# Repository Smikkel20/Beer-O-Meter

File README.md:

# Beer-O-Meter

A fun ATTiny-powered device that measures how quickly you can down a pint. Place a glass on the pressure plate, press the button, drink, and release — the 7-segment display shows your elapsed time in centiseconds.

## Features

- **Pressure plate / button trigger** — starts timing when pressed, stops when released.
- **TM1637 4-digit 7-segment display** — shows elapsed time live.
- **Auto-reset** — after a short cooldown, the meter is ready for the next round.
- **KiCad PCB** — custom PCB design included.

## Hardware

| Component | Description |
|-----------|-------------|
| ATTiny85 | 8-bit AVR MCU |
| TM1637 4-digit 7-segment display | Clock & data interface |
| Momentary push button / pressure plate | Input on PB2 (physical pin 7) |
| Wires / custom PCB | Connections as per KiCad design |

### Wiring

| Display / Button Pin | ATTiny85 Pin |
|----------------------|--------------|
| TM1637 CLK | PB4 (physical pin 3) |
| TM1637 DIO | PB3 (physical pin 2) |
| Button (pressure plate) | PB2 (physical pin 7) |

## Usage

1. Power the PCB.
2. Place your glass on the pressure plate.
3. Pick up the glass and start drinking!
4. Put down the glass on the pressure plate when its empty.
5. The display shows your time!

## Building & Flashing

Install the ATTiny85 core (e.g. via [ATTinyCore](https://github.com/SpenceKonde/ATTinyCore)) and flash with your programmer (USBasp, AVRISP mkII, Arduino-as-ISP, etc.):

```bash
arduino-cli compile --fqbn attiny:avr:attiny85 Beer-O-Meter/
arduino-cli upload -p /dev/ttyUSB0 --fqbn attiny:avr:attiny85 Beer-O-Meter/
```

Or open `Beer-O-Meter/Beer-O-Meter.ino` in the Arduino IDE with the ATTiny85 board selected and upload.

## PCB Design

The `PCB-Design/` folder contains the KiCad project files:

- `Beer-Timer.kicad_sch` — schematic
- `Beer-Timer.kicad_pcb` — PCB layout
- `Beer-Timer.kicad_pro` — project settings
- `Beer-Timer.step` / `Beer-Timer.stl` — 3D models

Open the `.kicad_pro` file in KiCad 7+ to view or modify the design.

## License

This project is licensed under the GNU General Public License v3.0 — see [LICENSE](LICENSE).

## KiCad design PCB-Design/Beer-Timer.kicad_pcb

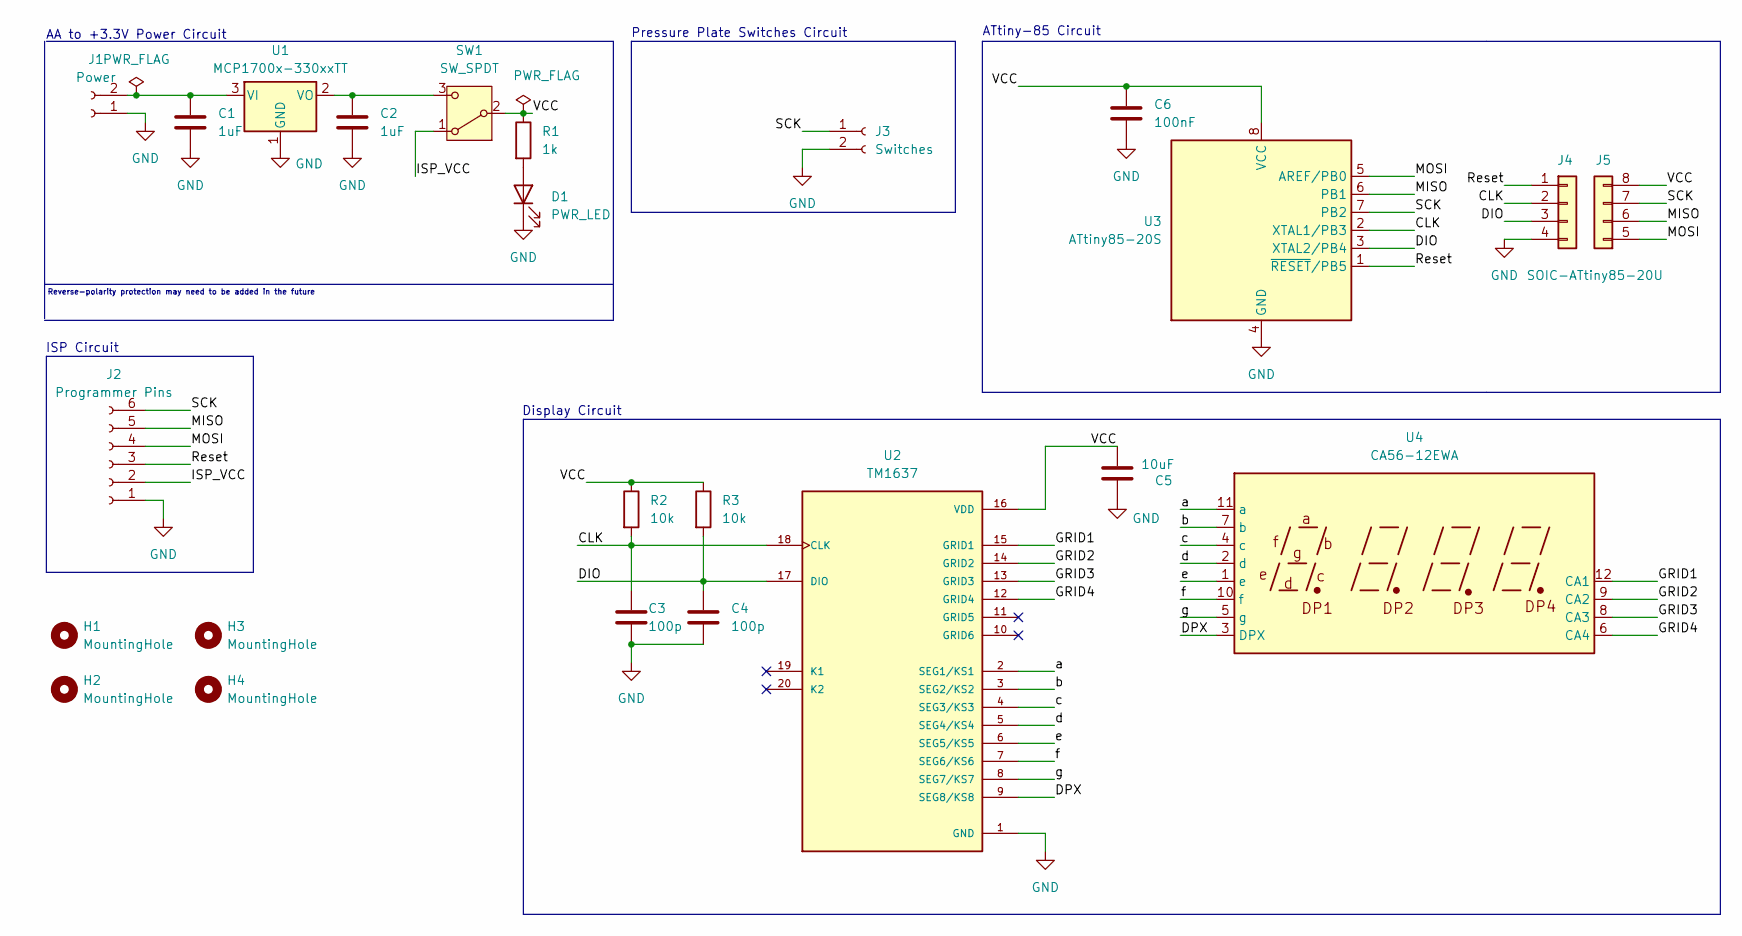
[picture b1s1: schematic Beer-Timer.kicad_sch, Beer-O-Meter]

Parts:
C1, C2: 1uF; C_0603_1608Metric_Pad1.08x0.95mm_HandSolder
C3, C4: 100p; C_0603_1608Metric_Pad1.08x0.95mm_HandSolder
C5: 10uF; C_0603_1608Metric_Pad1.08x0.95mm_HandSolder
C6: 100nF; C_0603_1608Metric_Pad1.08x0.95mm_HandSolder
D1: PWR_LED; LED_0603_1608Metric_Pad1.05x0.95mm_HandSolder
H1, H2, H3, H4: MountingHole; MountingHole_2.2mm_M2
J1: Power; PinHeader_1x02_P2.54mm_Vertical
J2: Programmer Pins; PinHeader_1x06_P2.54mm_Vertical
J3: Switches; PinHeader_1x02_P2.54mm_Vertical
J4: SOIC-ATtiny85-20U; PinHeader_1x04_P2.54mm_Vertical
J5: SOIC-2; PinHeader_1x04_P2.54mm_Vertical
R1: 1k; R_0603_1608Metric_Pad0.98x0.95mm_HandSolder
R2, R3: 10k; R_0603_1608Metric_Pad0.98x0.95mm_HandSolder
SW1: SW_SPDT; SW_SPDT_Shouhan_MSK12C02
U1: MCP1700x-330xxTT; SOT-23
U2: TM1637; SOP-20_7.5x12.8mm_P1.27mm; PARTREV v2.5
U3: ATtiny85-20S; SOIC-8_5.3x5.3mm_P1.27mm
U4: CA56-12EWA

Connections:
/CLK: C3.1, J4.2, R2.2, U2.18 (CLK), U3.2 (XTAL1/PB3)
/DIO: C4.1, J4.3, R3.2, U2.17 (DIO), U3.3 (XTAL2/PB4)
/DPX: U2.9 (SEG8/KS8), U4.3 (DPX)
/GRID1: U2.15 (GRID1), U4.12 (CA1)
/GRID2: U2.14 (GRID2), U4.9 (CA2)
/GRID3: U2.13 (GRID3), U4.8 (CA3)
/GRID4: U2.12 (GRID4), U4.6 (CA4)
/ISP_VCC: J2.2, SW1.1 (A)
/MISO: J2.5, J5.6, U3.6 (PB1)
/MOSI: J2.4, J5.5, U3.5 (AREF/PB0)
/Reset: J2.3, J4.1, U3.1 (~RESET/PB5)
/SCK: J2.6, J3.1, J5.7, U3.7 (PB2)
/VCC: C5.2, C6.1, J5.8, R1.1, R2.1, R3.1, SW1.2 (B), U2.16 (VDD), U3.8 (VCC)
/a: U2.2 (SEG1/KS1), U4.11 (a)
/b: U2.3 (SEG2/KS2), U4.7 (b)
/c: U2.4 (SEG3/KS3), U4.4 (c)
/d: U2.5 (SEG4/KS4), U4.2 (d)
/e: U2.6 (SEG5/KS5), U4.1 (e)
/f: U2.7 (SEG6/KS6), U4.10 (f)
/g: U2.8 (SEG7/KS7), U4.5 (g)
GND: C1.2, C2.2, C3.2, C4.2, C5.1, C6.2, D1.1 (K), J1.1, J2.1, J3.2, J4.4, U1.1 (GND), U2.1 (GND), U3.4 (GND); also elsewhere on the board
unnamed 21: D1.2 (A), R1.2; also elsewhere on the board
unnamed: C1.1, J1.2, U1.3 (VI)
unnamed: C2.1, SW1.3 (C), U1.2 (VO)

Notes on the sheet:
ISP Circuit
AA to +3.3V Power Circuit
Display Circuit
ATtiny-85 Circuit
Pressure Plate Switches Circuit
Reverse-polarity protection may need to be added in the future

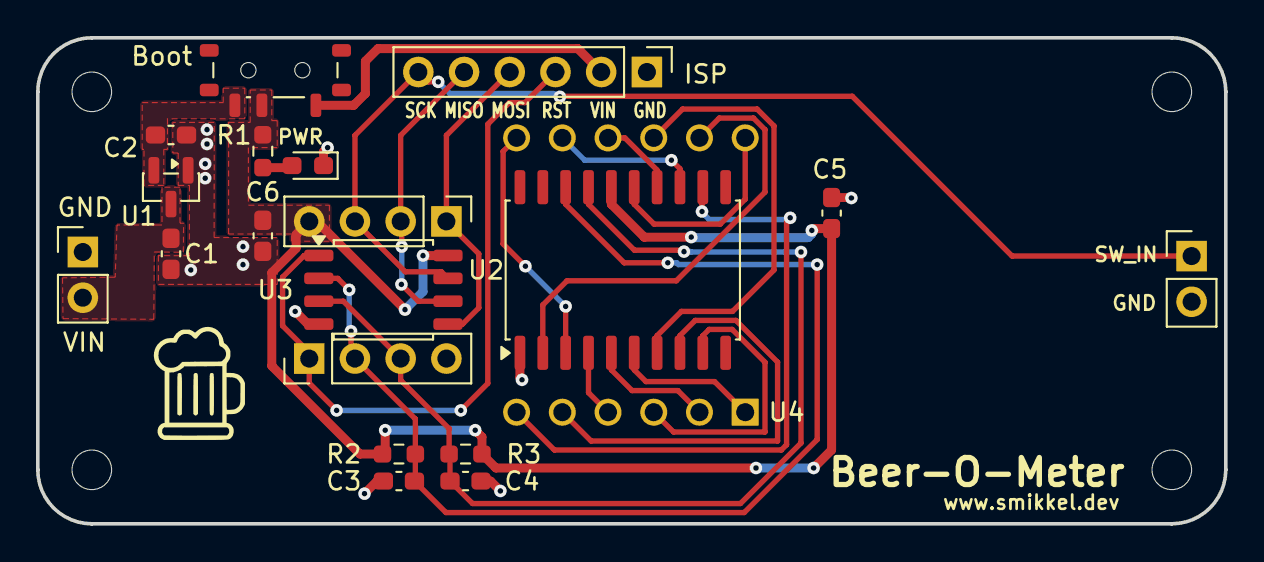
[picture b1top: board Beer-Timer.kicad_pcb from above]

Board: 2 copper layers, 66.0 x 27.0 mm, 24 parts (1 on the bottom side), 24 nets.

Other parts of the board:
PWR: PWR_LED; LED_0603_1608Metric_Pad1.05x0.95mm_HandSolder

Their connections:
GND: PWR.1 (K); also elsewhere on the board
unnamed 21: PWR.2 (A); also elsewhere on the board

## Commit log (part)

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2026-05-04 Updated for the ATtiny85
    Code for the microcontroller has been reworked for the new ATtiny85 instead of the Arduino for less power usage.
2026-05-04 Create .gitignore
    gitignore for KiCad
2026-05-04 Added the PCB Design
